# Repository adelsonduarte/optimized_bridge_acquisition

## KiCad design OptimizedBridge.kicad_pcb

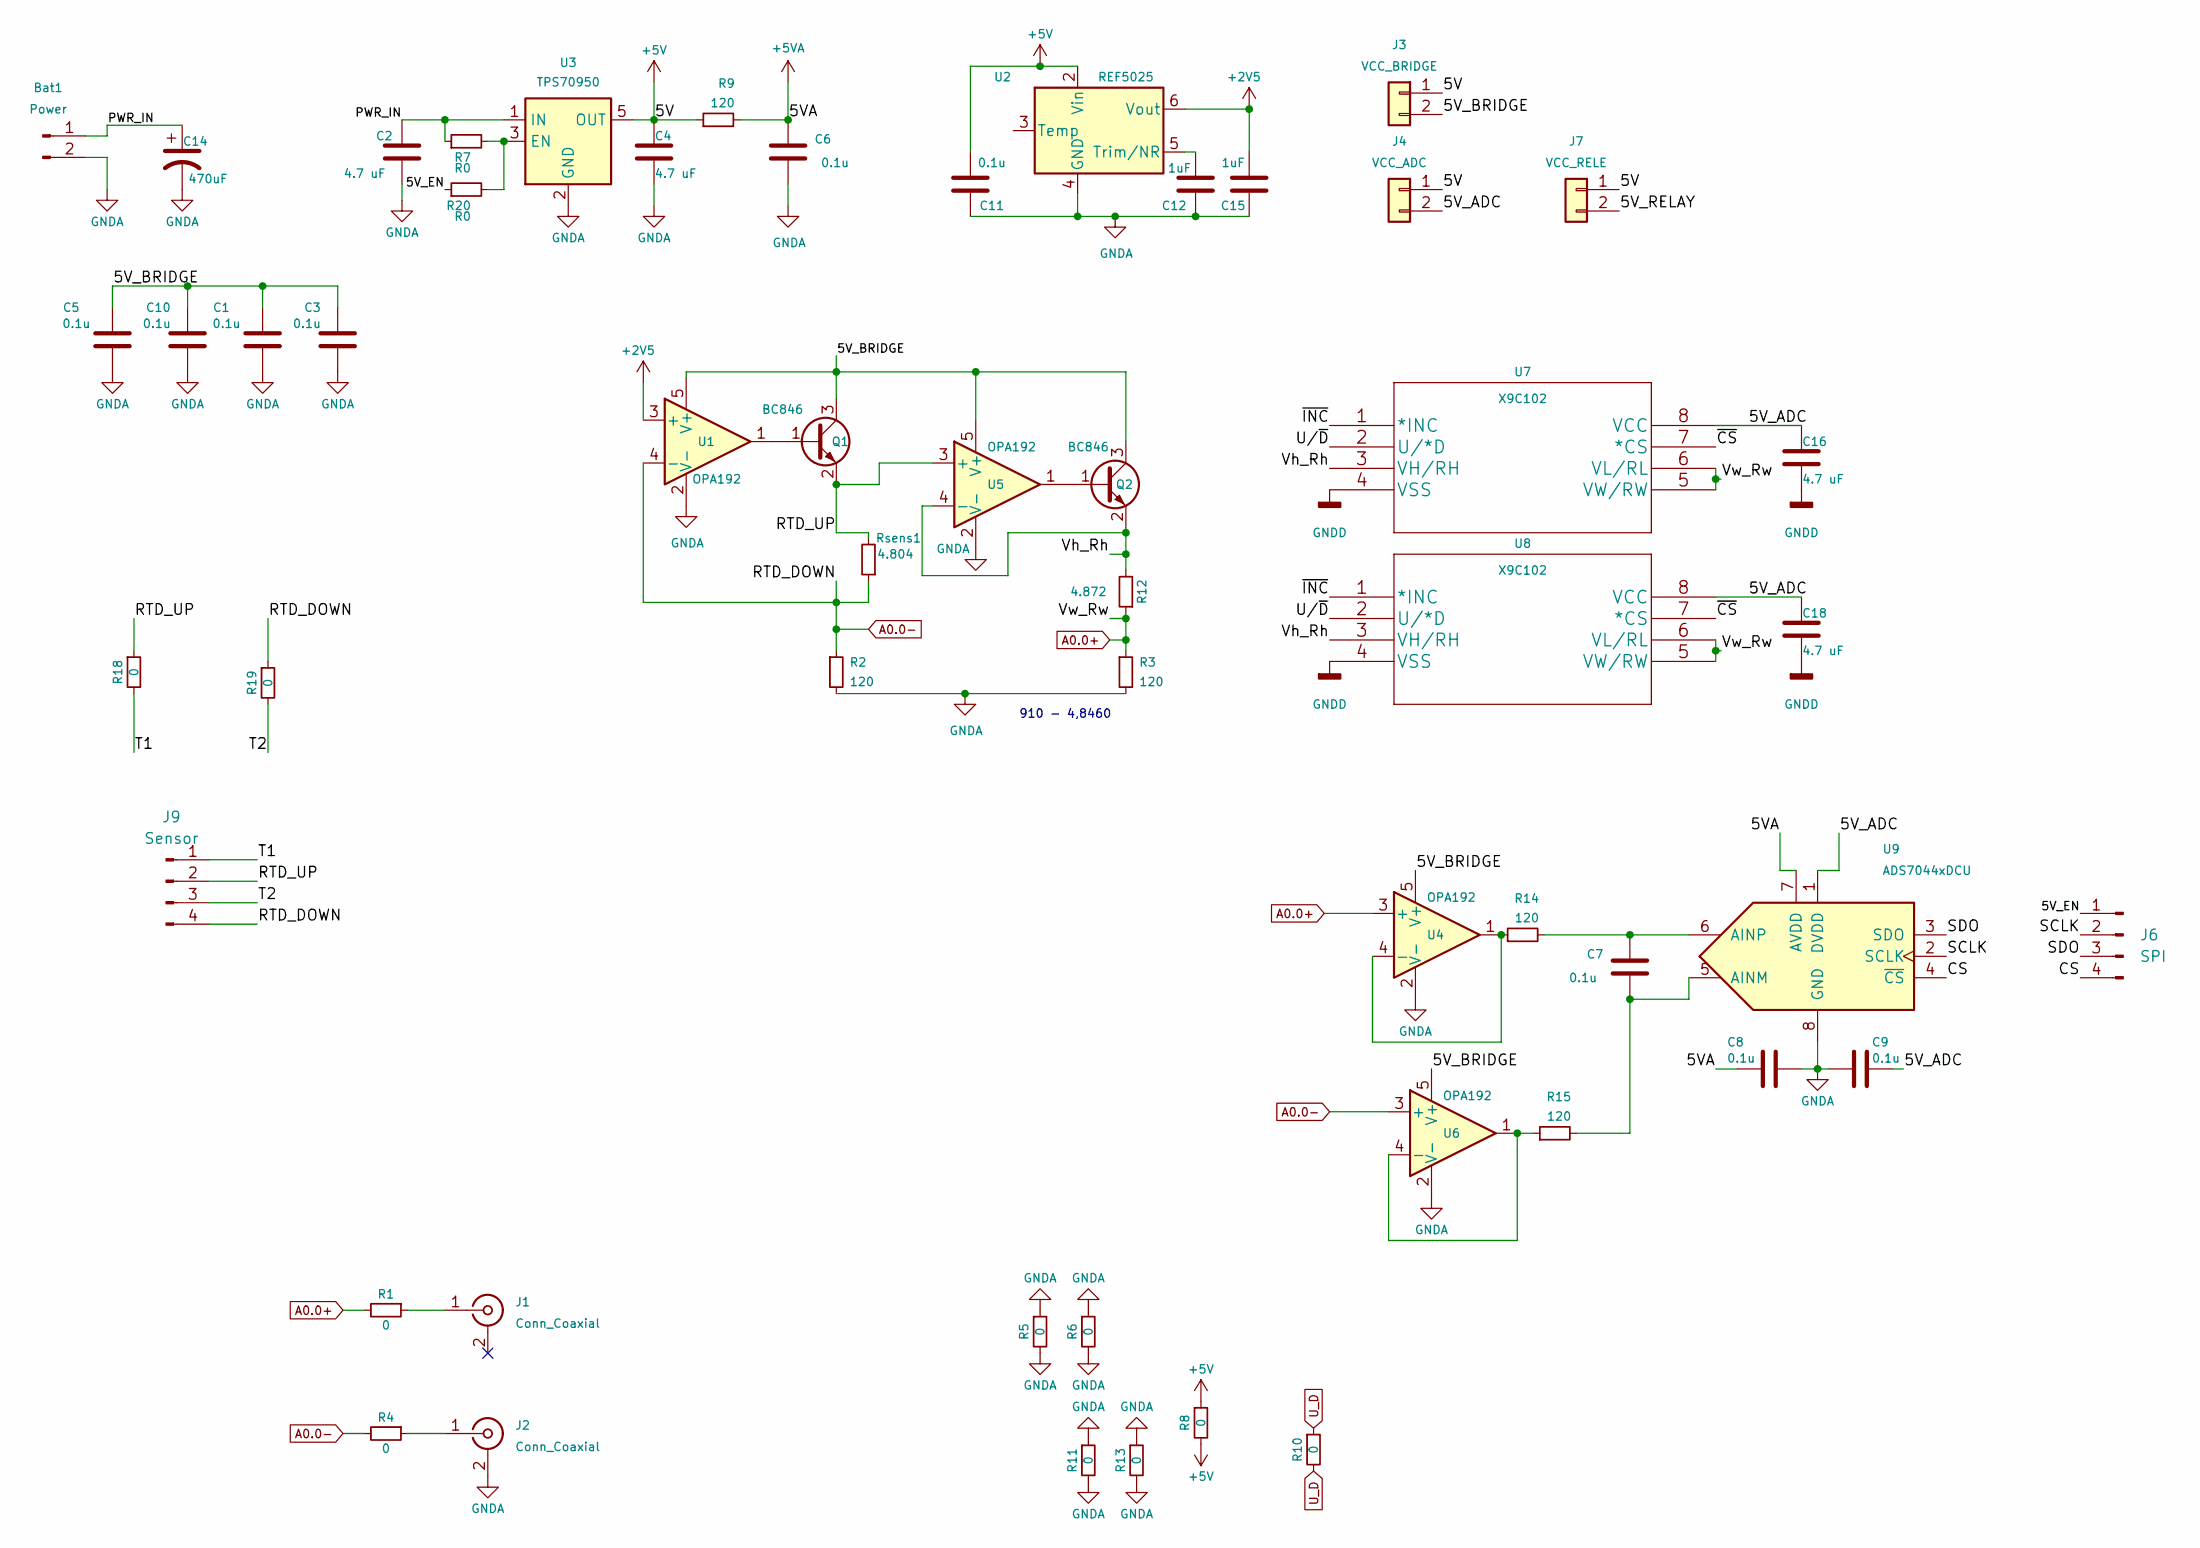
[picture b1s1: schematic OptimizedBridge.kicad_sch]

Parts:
Bat1: Power; Molex_KK-254_AE-6410-02A_1x02_P2.54mm_Vertical
C1, C3, C5, C6, C7, C8, C9, C10, C11: 0.1u; C_1206_3216Metric
C2, C4, C16, C18: 4.7 uF; C_1206_3216Metric_Pad1.42x1.75mm_HandSolder
C12, C15: 1uF; C_1206_3216Metric
C14: 470uF; CP_Elec_10x14.3
J1, J2: Conn_Coaxial; BNC_TEConnectivity_1478035_Horizontal
J3: VCC_BRIDGE; PinHeader_1x02_P2.54mm_Vertical
J4: VCC_ADC; PinHeader_1x02_P2.54mm_Vertical
J6: SPI; Molex_KK-254_AE-6410-04A_1x04_P2.54mm_Vertical
J7: VCC_RELE; PinHeader_1x02_P2.54mm_Vertical
J9: Sensor; Molex_KK-254_AE-6410-04A_1x04_P2.54mm_Vertical
Q1, Q2: BC846; SOT-23
R1, R4, R18, R19: 0; R_1206_3216Metric_Pad1.30x1.75mm_HandSolder
R2, R3: 120; R_Axial_DIN0204_L3.6mm_D1.6mm_P5.08mm_Horizontal
R5, R6, R8, R10, R11, R13: 0; R_1206_3216Metric_Pad1.42x1.75mm_HandSolder
R7, R20: R0; R_1206_3216Metric_Pad1.30x1.75mm_HandSolder
R9, R14, R15: 120; R_1206_3216Metric_Pad1.30x1.75mm_HandSolder
R12: 4.872; R_Axial_DIN0204_L3.6mm_D1.6mm_P5.08mm_Horizontal
Rsens1: 4.804; R_Axial_DIN0204_L3.6mm_D1.6mm_P5.08mm_Horizontal
U1, U4, U5, U6: OPA192; SOT-23-5_HandSoldering
U2: REF5025; MSOP-8_3x3mm_P0.65mm
U3: TPS70950; SOT-23-5
U7, U8: X9C102
U9: ADS7044xDCU; VSSOP-8_2.3x2mm_P0.5mm

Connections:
+2V5: C15.2, U1.3 (+), U2.6 (Vout)
+5V: C4.1, C11.2, J3.1, J4.1, J7.1, R8.1, R8.2, R9.1, U2.2 (Vin), U3.5 (OUT)
+5VA: C6.2, C8.2, R9.2, U9.7 (AVDD)
/5V_ADC: C9.1, C16.1, C18.1, J4.2, U7.8 (VCC), U8.8 (VCC), U9.1 (DVDD)
/5V_BRIDGE: C1.2, C3.2, C5.2, C10.2, J3.2, Q1.3 (C), Q2.3 (C), U1.5 (V+), U4.5 (V+), U5.5 (V+), U6.5 (V+)
/5V_EN: J6.1, R20.1
/5V_RELAY: J7.2
/CS: J6.4, U9.4 (~CS)
/PWR_IN: Bat1.1, C2.1, C14.1, R7.1, U3.1 (IN)
/RTD_UP: J9.2, Q1.2 (E), R18.1, Rsens1.2, U5.3 (+)
/SCLK: J6.2, U9.2 (SCLK)
/SDO: J6.3, U9.3 (SDO)
/T1: J9.1, R18.2
/T2: J9.3, R19.2
/U/~D: U7.2 (U/*D), U8.2 (U/*D)
/Vh_Rh: Q2.2 (E), R12.2, U5.4 (-), U7.3 (VH/RH), U8.3 (VH/RH)
/~CS: U7.7 (*CS), U8.7 (*CS)
/~INC: U7.1 (*INC), U8.1 (*INC)
A0.0+: R1.2, R3.1, R12.1, U4.3 (+), U7.5 (VW/RW), U7.6 (VL/RL), U8.5 (VW/RW), U8.6 (VL/RL)
A0.0-: J9.4, R2.1, R4.2, R19.1, Rsens1.1, U1.4 (-), U6.3 (+)
GNDA: Bat1.2, C1.1, C2.2, C3.1, C4.2, C5.1, C6.1, C8.1, C9.2, C10.1, C11.1, C12.1, C14.2, C15.1, J2.2 (Ext), R2.2, R3.2, R5.1, R5.2, R6.1, R6.2, R11.1, R11.2, R13.1, R13.2, U1.2 (V-), U2.4 (GND), U3.2 (GND), U4.2 (V-), U5.2 (V-), U6.2 (V-), U9.8 (GND)
GNDD: C16.2, C18.2, U7.4 (VSS), U8.4 (VSS)
unnamed: C7.1, R15.2, U9.5 (AINM)
unnamed: C7.2, R14.2, U9.6 (AINP)
unnamed: C12.2, U2.5 (Trim/NR)
unnamed: J1.1 (In), R1.1
unnamed: J2.1 (In), R4.1
unnamed: Q1.1 (B), U1.1
unnamed: Q2.1 (B), U5.1
unnamed: R7.2, R20.2, U3.3 (EN)
unnamed: R14.1, U4.1, U4.4 (-)
unnamed: R15.1, U6.1, U6.4 (-)
U_D: R10.1, R10.2

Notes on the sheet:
910 - 4,8460

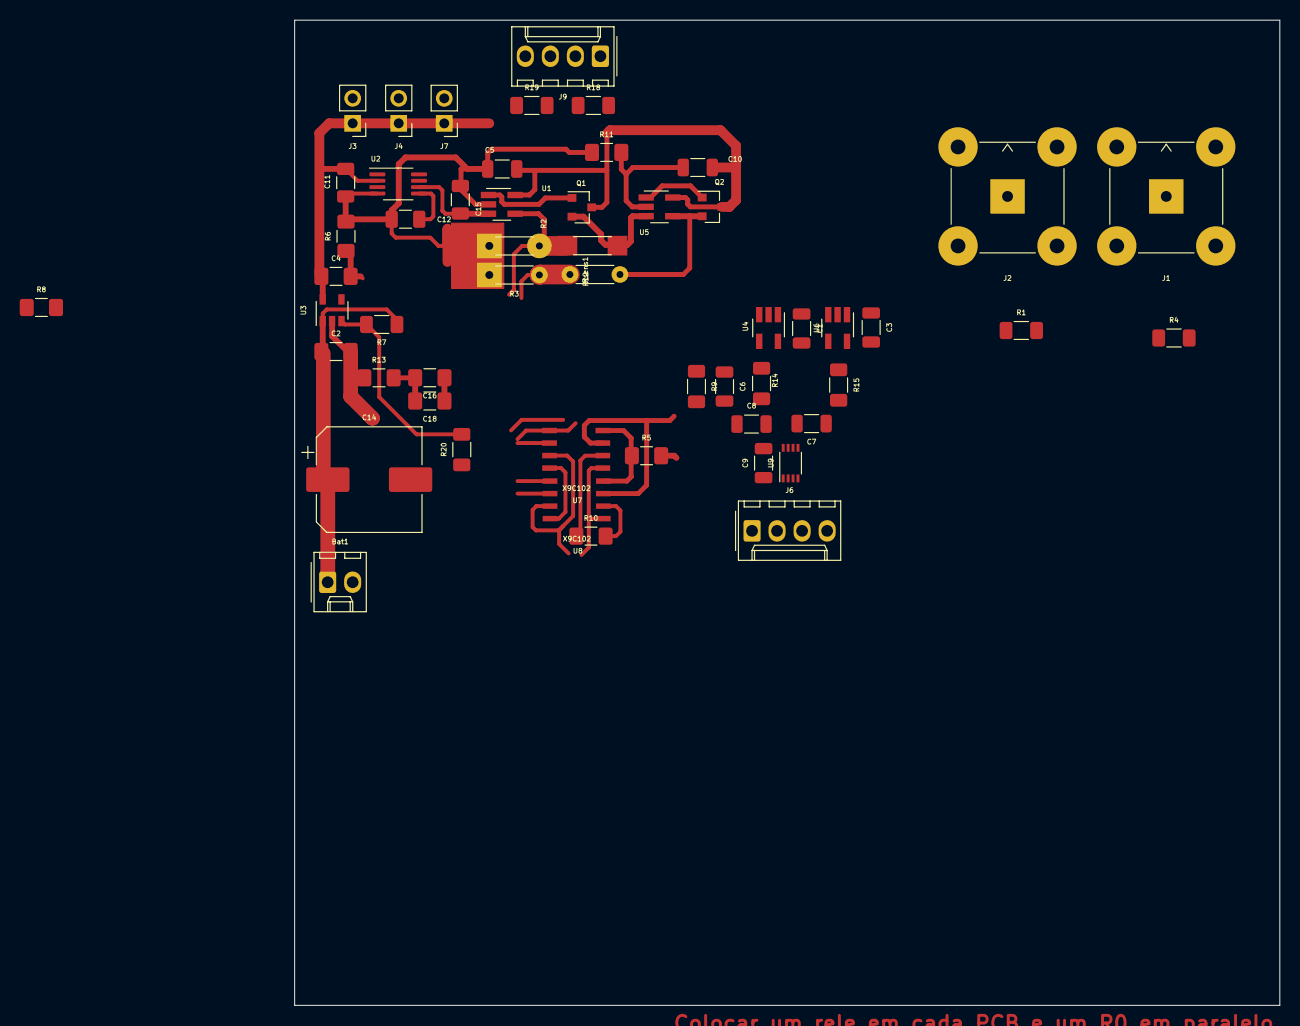
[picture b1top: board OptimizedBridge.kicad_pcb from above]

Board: 2 copper layers, 100.0 x 100.0 mm, 54 parts (0 on the bottom side), 32 nets.

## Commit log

2023-02-20 Start design
